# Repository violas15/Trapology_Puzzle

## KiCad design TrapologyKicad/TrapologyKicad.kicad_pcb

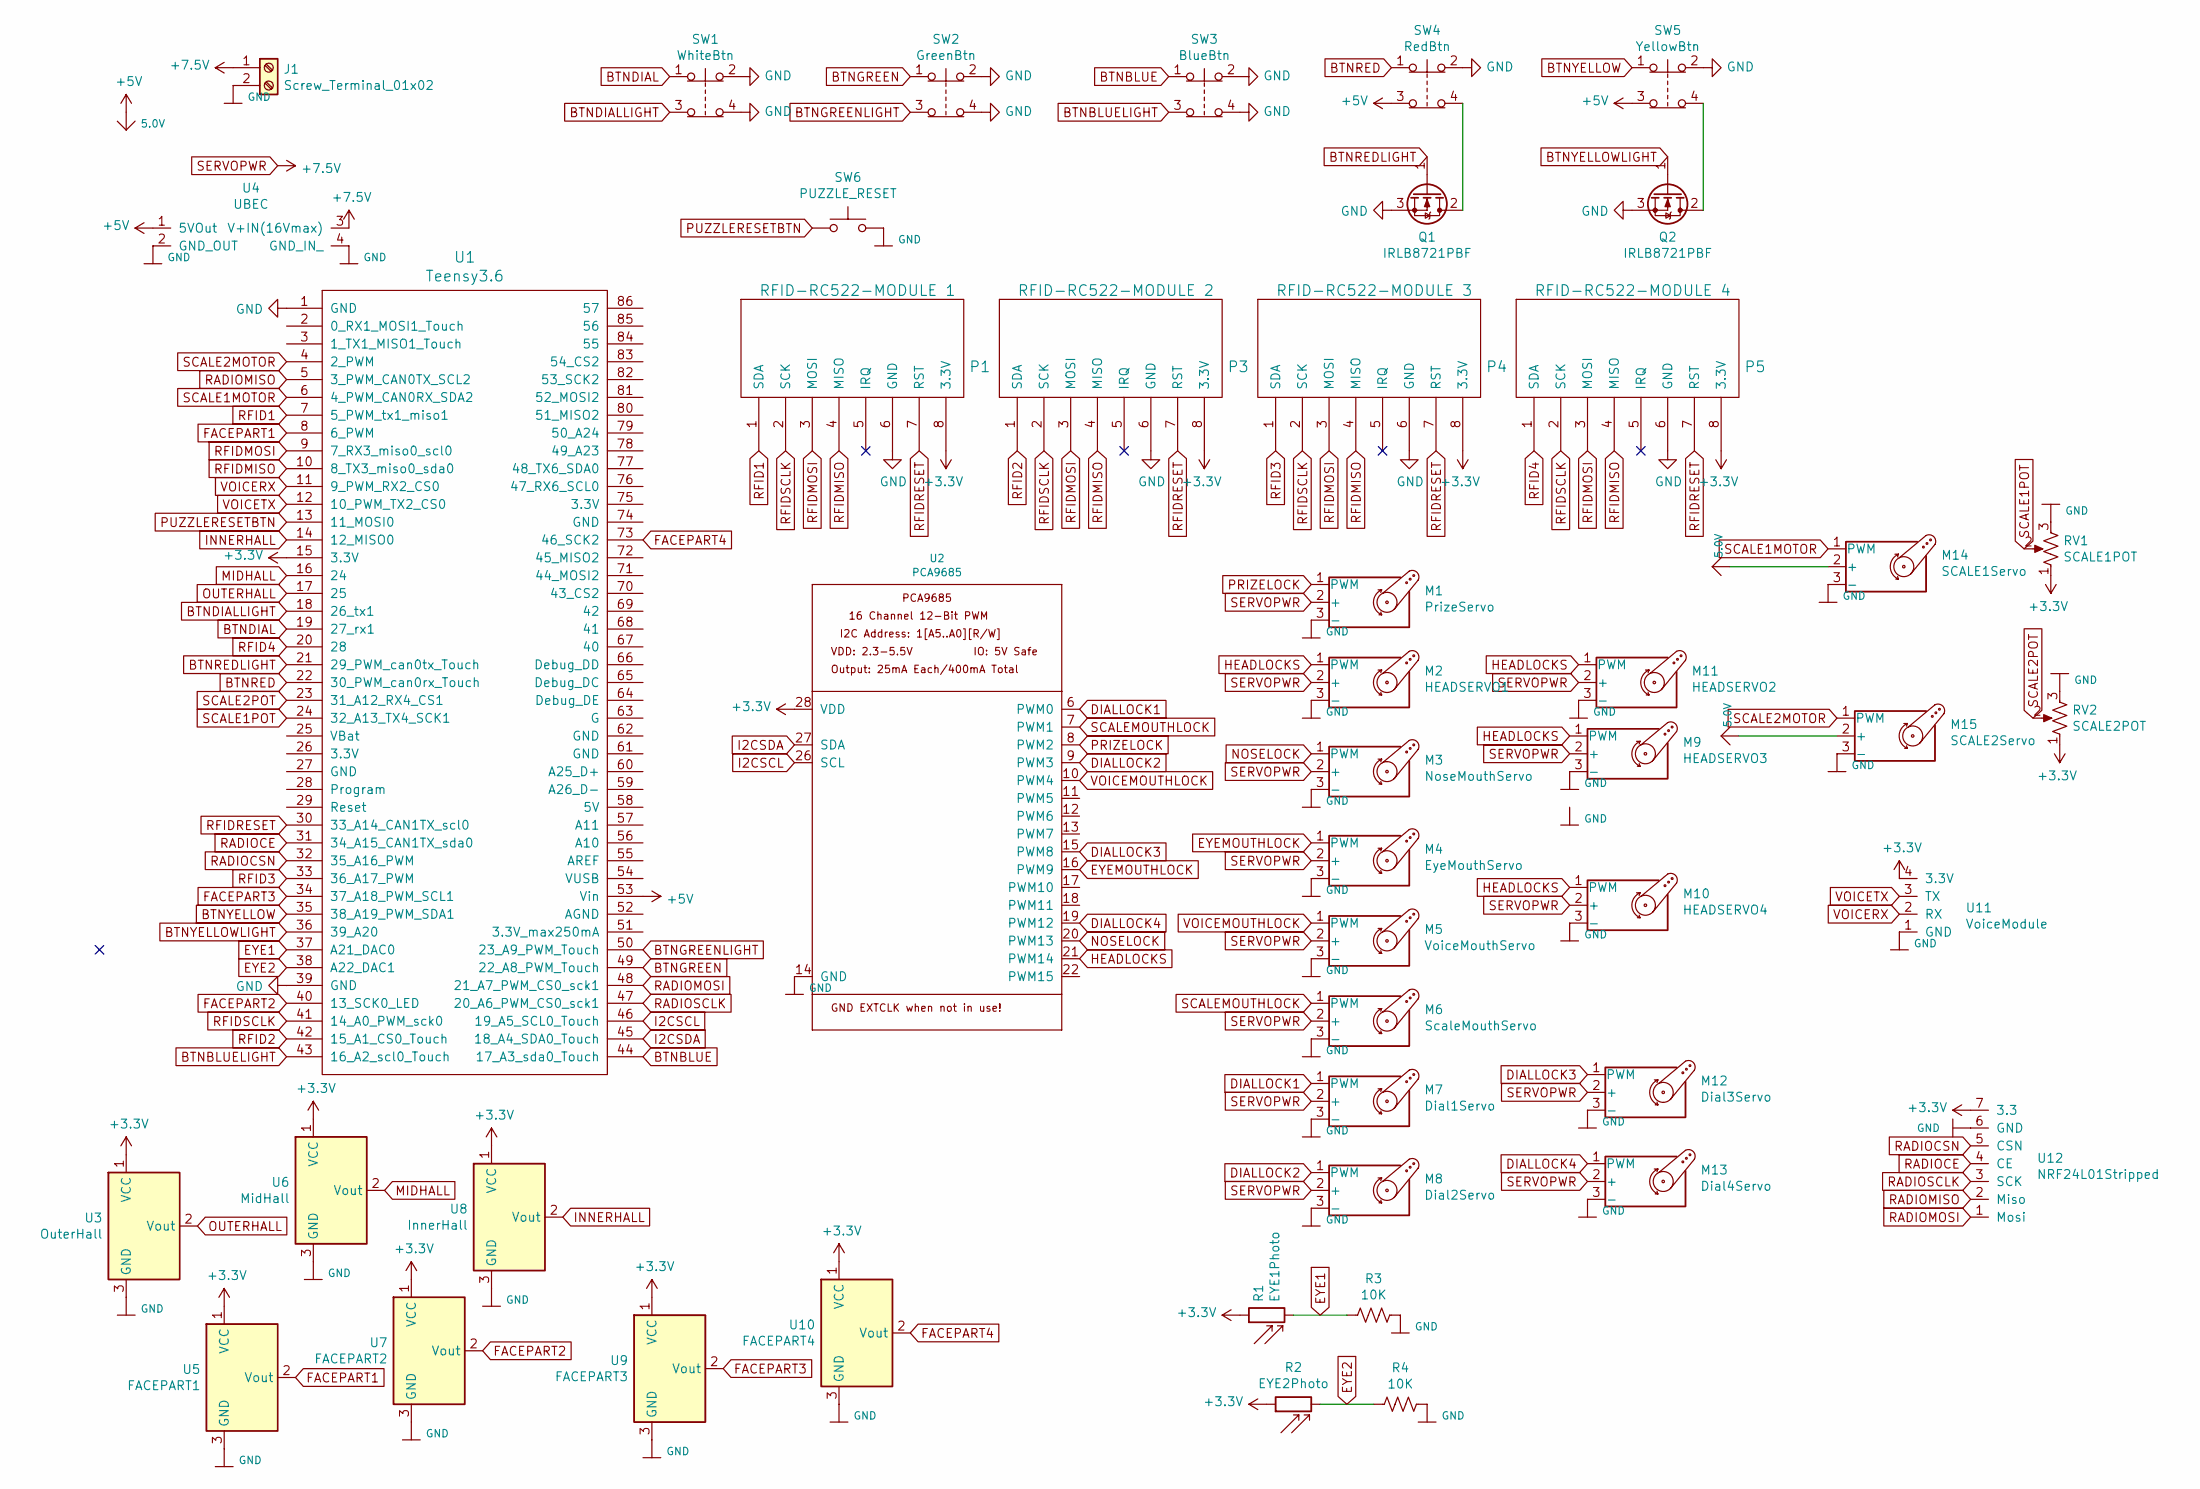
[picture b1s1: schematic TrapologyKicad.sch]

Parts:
J1: Screw_Terminal_01x02; TerminalBlock_Altech_AK300-2_P5.00mm
M1: PrizeServo; PinSocket_1x03_P2.54mm_Vertical
M2: HEADSERVO1; PinSocket_1x03_P2.54mm_Vertical
M3: NoseMouthServo; PinSocket_1x03_P2.54mm_Vertical
M4: EyeMouthServo; PinSocket_1x03_P2.54mm_Vertical
M5: VoiceMouthServo; PinSocket_1x03_P2.54mm_Vertical
M6: ScaleMouthServo; PinSocket_1x03_P2.54mm_Vertical
M7: Dial1Servo; PinSocket_1x03_P2.54mm_Vertical
M8: Dial2Servo; PinSocket_1x03_P2.54mm_Vertical
M9: HEADSERVO3; PinSocket_1x03_P2.54mm_Vertical
M10: HEADSERVO4; PinSocket_1x03_P2.54mm_Vertical
M11: HEADSERVO2; PinSocket_1x03_P2.54mm_Vertical
M12: Dial3Servo; PinSocket_1x03_P2.54mm_Vertical
M13: Dial4Servo; PinSocket_1x03_P2.54mm_Vertical
M14: SCALE1Servo; PinSocket_1x03_P2.54mm_Vertical
M15: SCALE2Servo; PinSocket_1x03_P2.54mm_Vertical
P1: RFID-RC522-MODULE 1; PinSocket_1x08_P2.54mm_Vertical
P3: RFID-RC522-MODULE 2; PinSocket_1x08_P2.54mm_Vertical
P4: RFID-RC522-MODULE 3; PinSocket_1x08_P2.54mm_Vertical
P5: RFID-RC522-MODULE 4; PinSocket_1x08_P2.54mm_Vertical
Q1, Q2: IRLB8721PBF; TO-220-3_Vertical
R1: EYE1Photo; PinSocket_1x02_P2.54mm_Vertical
R2: EYE2Photo; PinSocket_1x02_P2.54mm_Vertical
R3, R4: 10K; R_Axial_DIN0411_L9.9mm_D3.6mm_P12.70mm_Horizontal
RV1: SCALE1POT; PinSocket_1x03_P2.54mm_Vertical
RV2: SCALE2POT; PinSocket_1x03_P2.54mm_Vertical
SW1: WhiteBtn; PinSocket_1x04_P2.54mm_Vertical
SW2: GreenBtn; PinSocket_1x04_P2.54mm_Vertical
SW3: BlueBtn; PinSocket_1x04_P2.54mm_Vertical
SW4: RedBtn; PinSocket_1x04_P2.54mm_Vertical
SW5: YellowBtn; PinSocket_1x04_P2.54mm_Vertical
SW6: PUZZLE_RESET; PinSocket_1x02_P2.54mm_Vertical
U1: Teensy3.6; Teensy35_36
U2: PCA9685; 16ChannelPWM
U3: OuterHall; PinSocket_1x03_P2.54mm_Vertical
U4: UBEC
U5: FACEPART1; PinSocket_1x03_P2.54mm_Vertical
U6: MidHall; PinSocket_1x03_P2.54mm_Vertical
U7: FACEPART2; PinSocket_1x03_P2.54mm_Vertical
U8: InnerHall; PinSocket_1x03_P2.54mm_Vertical
U9: FACEPART3; PinSocket_1x03_P2.54mm_Vertical
U10: FACEPART4; PinSocket_1x03_P2.54mm_Vertical
U11: VoiceModule; PinSocket_1x04_P2.54mm_Vertical
U12: NRF24L01Stripped; PinSocket_1x07_P2.54mm_Vertical

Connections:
+3V3: P1.8 (3.3V), P3.8 (3.3V), P4.8 (3.3V), P5.8 (3.3V), R1.1, R2.1, RV1.1, RV2.1, U1.15 (3.3V), U2.28 (VDD), U3.1 (VCC), U5.1 (VCC), U6.1 (VCC), U7.1 (VCC), U8.1 (VCC), U9.1 (VCC), U10.1 (VCC), U11.4 (3.3V), U12.7 (3.3)
+5V: M14.2 (+), M15.2 (+), SW4.3, SW5.3, U1.53 (Vin), U4.1 (5VOut)
BTNBLUE: SW3.1, U1.44 (17_A3_sda0_Touch)
BTNBLUELIGHT: SW3.3, U1.43 (16_A2_scl0_Touch)
BTNDIAL: SW1.1, U1.19 (27_rx1)
BTNDIALLIGHT: SW1.3, U1.18 (26_tx1)
BTNGREEN: SW2.1, U1.49 (22_A8_PWM_Touch)
BTNGREENLIGHT: SW2.3, U1.50 (23_A9_PWM_Touch)
BTNRED: SW4.1, U1.22 (30_PWM_can0rx_Touch)
BTNREDLIGHT: Q1.1 (G), U1.21 (29_PWM_can0tx_Touch)
BTNYELLOW: SW5.1, U1.35 (38_A19_PWM_SDA1)
BTNYELLOWLIGHT: Q2.1 (G), U1.36 (39_A20)
DIALLOCK1: M7.1 (PWM), U2.6 (PWM0)
DIALLOCK2: M8.1 (PWM), U2.9 (PWM3)
DIALLOCK3: M12.1 (PWM), U2.15 (PWM8)
DIALLOCK4: M13.1 (PWM), U2.19 (PWM12)
EYE1: R1.2, R3.2, U1.37 (A21_DAC0)
EYE2: R2.2, R4.2, U1.38 (A22_DAC1)
EYEMOUTHLOCK: M4.1 (PWM), U2.16 (PWM9)
FACEPART1: U1.8 (6_PWM), U5.2 (Vout)
FACEPART2: U1.40 (13_SCK0_LED), U7.2 (Vout)
FACEPART3: U1.34 (37_A18_PWM_SCL1), U9.2 (Vout)
FACEPART4: U1.73 (46_SCK2), U10.2 (Vout)
GND: J1.2, M1.3 (-), M2.3 (-), M3.3 (-), M4.3 (-), M5.3 (-), M6.3 (-), M7.3 (-), M8.3 (-), M9.3 (-), M10.3 (-), M11.3 (-), M12.3 (-), M13.3 (-), M14.3 (-), M15.3 (-), P1.6 (GND), P3.6 (GND), P4.6 (GND), P5.6 (GND), Q1.3 (S), Q2.3 (S), R3.1, R4.1, RV1.3, RV2.3, SW1.2, SW1.4, SW2.2, SW2.4, SW3.2, SW3.4, SW4.2, SW5.2, SW6.2, U1.1 (GND), U1.39 (GND), U2.14 (GND), U3.3 (GND), U4.2 (GND_OUT), U4.4 (GND_IN_), U5.3 (GND), U6.3 (GND), U7.3 (GND), U8.3 (GND), U9.3 (GND), U10.3 (GND), U11.1 (GND), U12.6 (GND)
HEADLOCKS: M2.1 (PWM), M9.1 (PWM), M10.1 (PWM), M11.1 (PWM), U2.21 (PWM14)
I2CSCL: U1.46 (19_A5_SCL0_Touch), U2.26 (SCL)
I2CSDA: U1.45 (18_A4_SDA0_Touch), U2.27 (SDA)
INNERHALL: U1.14 (12_MISO0), U8.2 (Vout)
MIDHALL: U1.16 (24), U6.2 (Vout)
NOSELOCK: M3.1 (PWM), U2.20 (PWM13)
unnamed: Q1.2 (D), SW4.4
unnamed: Q2.2 (D), SW5.4
OUTERHALL: U1.17 (25), U3.2 (Vout)
PRIZELOCK: M1.1 (PWM), U2.8 (PWM2)
PUZZLERESETBTN: SW6.1, U1.13 (11_MOSI0)
RADIOCE: U1.31 (34_A15_CAN1TX_sda0), U12.4 (CE)
RADIOCSN: U1.32 (35_A16_PWM), U12.5 (CSN)
RADIOMISO: U1.5 (3_PWM_CAN0TX_SCL2), U12.2 (Miso)
RADIOMOSI: U1.48 (21_A7_PWM_CS0_sck1), U12.1 (Mosi)
RADIOSCLK: U1.47 (20_A6_PWM_CS0_sck1), U12.3 (SCK)
RFID1: P1.1 (SDA), U1.7 (5_PWM_tx1_miso1)
RFID2: P3.1 (SDA), U1.42 (15_A1_CS0_Touch)
RFID3: P4.1 (SDA), U1.33 (36_A17_PWM)
RFID4: P5.1 (SDA), U1.20 (28)
RFIDMISO: P1.4 (MISO), P3.4 (MISO), P4.4 (MISO), P5.4 (MISO), U1.10 (8_TX3_miso0_sda0)
RFIDMOSI: P1.3 (MOSI), P3.3 (MOSI), P4.3 (MOSI), P5.3 (MOSI), U1.9 (7_RX3_miso0_scl0)
RFIDRESET: P1.7 (RST), P3.7 (RST), P4.7 (RST), P5.7 (RST), U1.30 (33_A14_CAN1TX_scl0)
RFIDSCLK: P1.2 (SCK), P3.2 (SCK), P4.2 (SCK), P5.2 (SCK), U1.41 (14_A0_PWM_sck0)
SCALE1MOTOR: M14.1 (PWM), U1.6 (4_PWM_CAN0RX_SDA2)
SCALE1POT: RV1.2, U1.24 (32_A13_TX4_SCK1)
SCALE2MOTOR: M15.1 (PWM), U1.4 (2_PWM)
SCALE2POT: RV2.2, U1.23 (31_A12_RX4_CS1)
SCALEMOUTHLOCK: M6.1 (PWM), U2.7 (PWM1)
SERVOPWR: J1.1, M1.2 (+), M2.2 (+), M3.2 (+), M4.2 (+), M5.2 (+), M6.2 (+), M7.2 (+), M8.2 (+), M9.2 (+), M10.2 (+), M11.2 (+), M12.2 (+), M13.2 (+), U4.3 (V+IN(16Vmax))
VOICEMOUTHLOCK: M5.1 (PWM), U2.10 (PWM4)
VOICERX: U1.11 (9_PWM_RX2_CS0), U11.2 (RX)
VOICETX: U1.12 (10_PWM_TX2_CS0), U11.3 (TX)

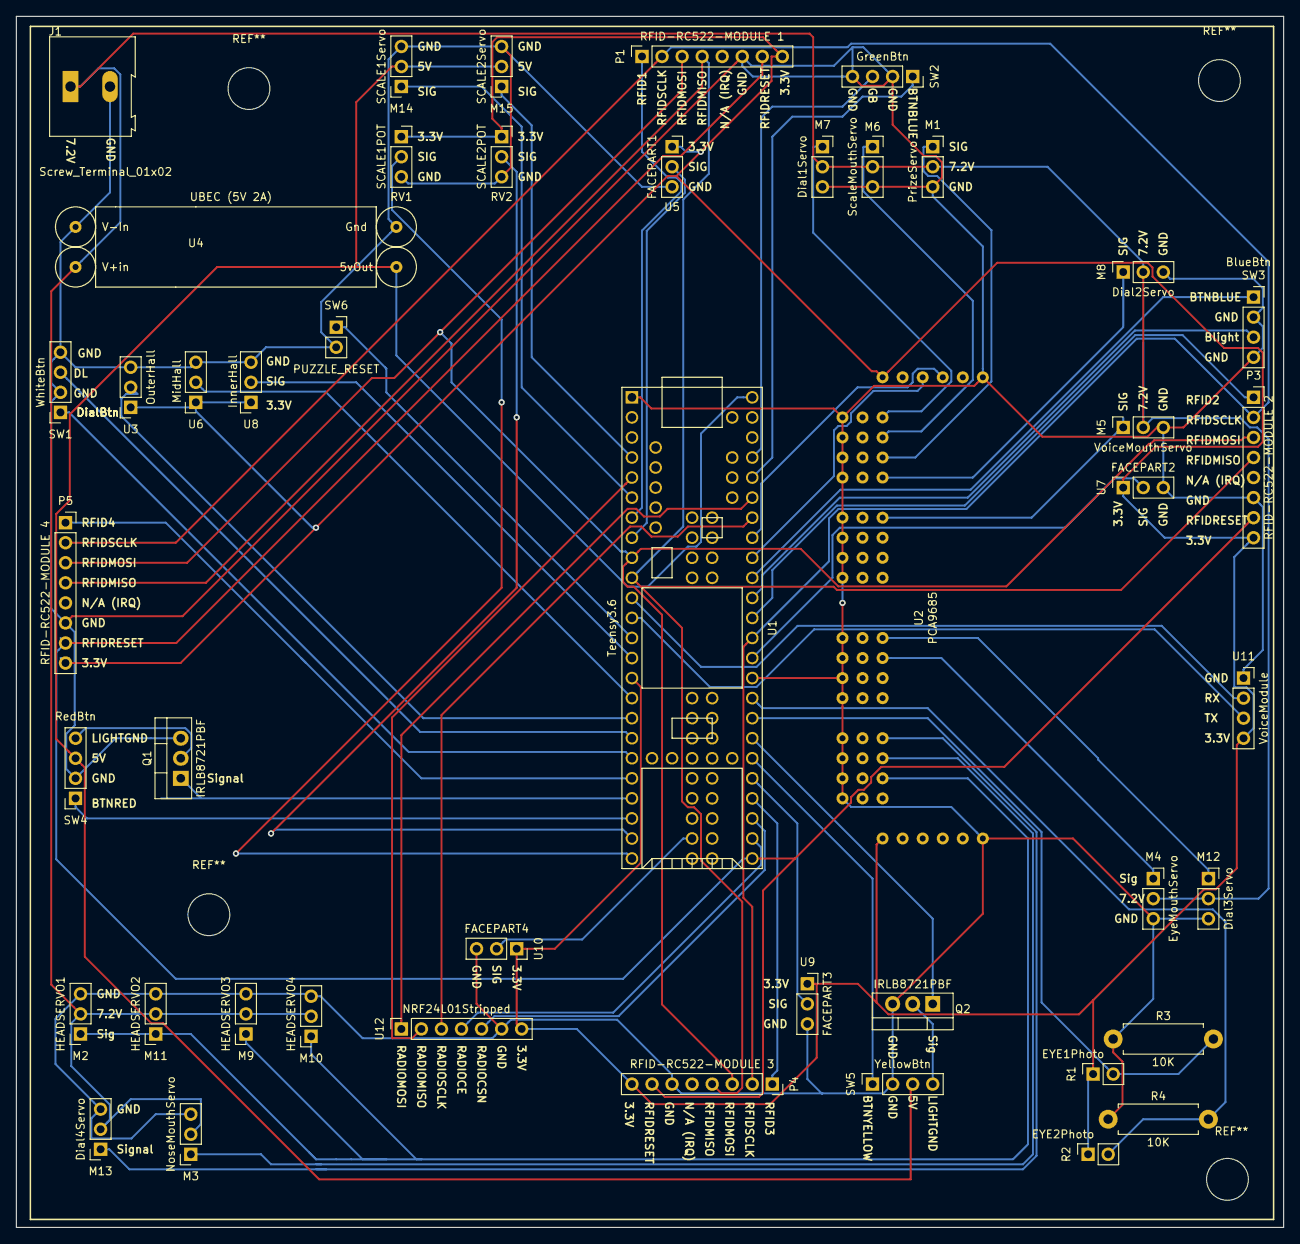
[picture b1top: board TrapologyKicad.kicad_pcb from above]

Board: 2 copper layers, 160.5 x 153.4 mm, 46 parts (0 on the bottom side), 57 nets.

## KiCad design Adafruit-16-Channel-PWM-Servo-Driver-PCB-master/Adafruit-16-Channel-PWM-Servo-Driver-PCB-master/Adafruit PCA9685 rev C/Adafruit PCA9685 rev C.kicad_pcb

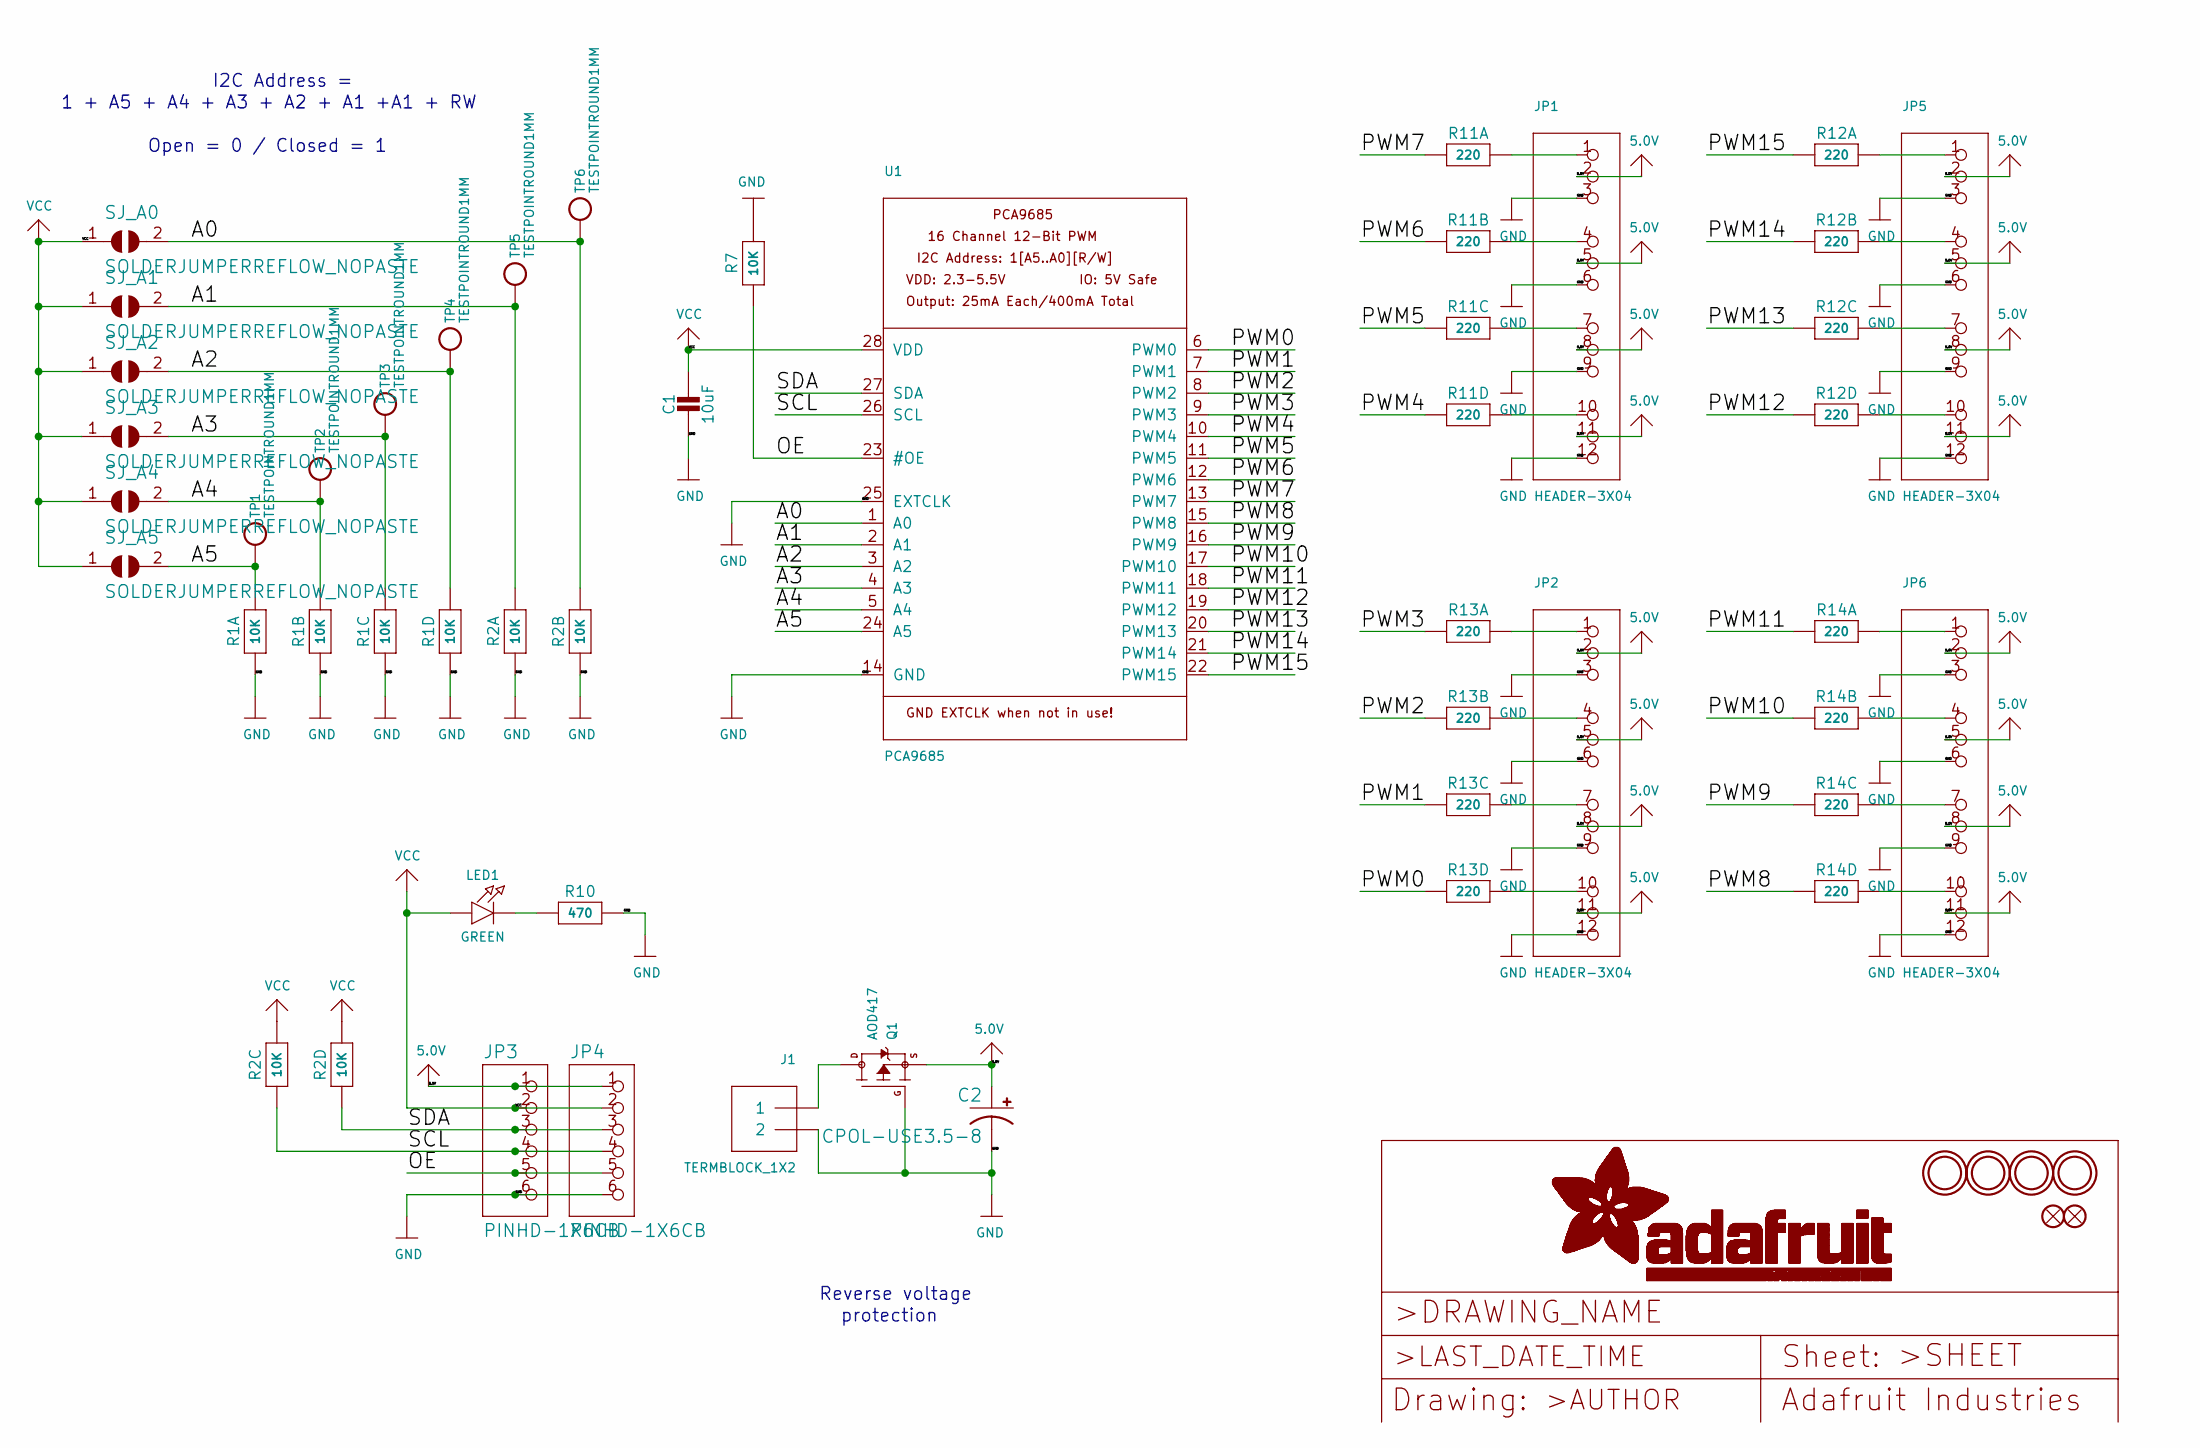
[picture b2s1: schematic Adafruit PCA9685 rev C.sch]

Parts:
C1: 10uF; 0805-NO
C2: CPOL-USE3.5-8; E3,5-8
FID1, FID2: FIDUCIAL\"\"; FIDUCIAL_1MM
J1: TERMBLOCK_1X2; TERMBLOCK_1X2-3.5MM
JP1, JP2, JP5, JP6: HEADER-3X04; 3X04
JP3, JP4: PINHD-1X6CB; 1X06-CLEANBIG
LED1: GREEN; CHIPLED_0805_NOOUTLINE
Q1: AOD417; TO252
R1, R2: 10K; RESPACK_4X0603
R7: 10K; 0805-NO
R10: 470; _0805MP
R11, R12, R13, R14: 220; RESPACK_4X0603
SJ_A0, SJ_A1, SJ_A2, SJ_A3, SJ_A4, SJ_A5: SOLDERJUMPERREFLOW_NOPASTE; SOLDERJUMPER_REFLOW_NOPASTE
TP1, TP2, TP3, TP4, TP5, TP6: TESTPOINTROUND1MM; TESTPOINT_ROUND_1MM
U1: PCA9685; TSSOP28
U$47, U$48, U$49, U$50: MOUNTINGHOLE2.5; MOUNTINGHOLE_2.5_PLATED

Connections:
5.0V: C2.+, JP1.2, JP1.5, JP1.8, JP1.11, JP2.2, JP2.5, JP2.8, JP2.11, JP3.1, JP4.1, JP5.2, JP5.5, JP5.8, JP5.11, JP6.2, JP6.5, JP6.8, JP6.11, Q1.2 (S)
/A0: R2.7 (2), SJ_A0.2, TP6.P$1, U1.1 (A0)
/A1: R2.8 (2), SJ_A1.2, TP5.P$1, U1.2 (A1)
/A2: R1.5 (2), SJ_A2.2, TP4.P$1, U1.3 (A2)
/A3: R1.6 (2), SJ_A3.2, TP3.P$1, U1.4 (A3)
/A4: R1.7 (2), SJ_A4.2, TP2.P$1, U1.5 (A4)
/A5: R1.8 (2), SJ_A5.2, TP1.P$1, U1.24 (A5)
/OE: JP3.5, JP4.5, R7.1, U1.23 (#OE)
/PWM0: R13.4 (1), U1.6 (PWM0)
/PWM1: R13.3 (1), U1.7 (PWM1)
/PWM2: R13.2 (1), U1.8 (PWM2)
/PWM3: R13.1, U1.9 (PWM3)
/PWM4: R11.4 (1), U1.10 (PWM4)
/PWM5: R11.3 (1), U1.11 (PWM5)
/PWM6: R11.2 (1), U1.12 (PWM6)
/PWM7: R11.1, U1.13 (PWM7)
/PWM8: R14.4 (1), U1.15 (PWM8)
/PWM9: R14.3 (1), U1.16 (PWM9)
/PWM10: R14.2 (1), U1.17 (PWM10)
/PWM11: R14.1, U1.18 (PWM11)
/PWM12: R12.4 (1), U1.19 (PWM12)
/PWM13: R12.3 (1), U1.20 (PWM13)
/PWM14: R12.2 (1), U1.21 (PWM14)
/PWM15: R12.1, U1.22 (PWM15)
/SCL: JP3.4, JP4.4, R2.3 (1), U1.26 (SCL)
/SDA: JP3.3, JP4.3, R2.4 (1), U1.27 (SDA)
GND: C1.2, C2.-, J1.2, JP1.3, JP1.6, JP1.9, JP1.12, JP2.3, JP2.6, JP2.9, JP2.12, JP3.6, JP4.6, JP5.3, JP5.6, JP5.9, JP5.12, JP6.3, JP6.6, JP6.9, JP6.12, Q1.1 (G), R1.1, R1.2 (1), R1.3 (1), R1.4 (1), R2.1, R2.2 (1), R7.2, R10.2, U1.14 (GND), U1.25 (EXTCLK)
unnamed: J1.1, Q1.3 (D)
unnamed: JP1.1, R11.8 (2)
unnamed: JP1.4, R11.7 (2)
unnamed: JP1.7, R11.6 (2)
unnamed: JP1.10, R11.5 (2)
unnamed: JP2.1, R13.8 (2)
unnamed: JP2.4, R13.7 (2)
unnamed: JP2.7, R13.6 (2)
unnamed: JP2.10, R13.5 (2)
unnamed: JP5.1, R12.8 (2)
unnamed: JP5.4, R12.7 (2)
unnamed: JP5.7, R12.6 (2)
unnamed: JP5.10, R12.5 (2)
unnamed: JP6.1, R14.8 (2)
unnamed: JP6.4, R14.7 (2)
unnamed: JP6.7, R14.6 (2)
unnamed: JP6.10, R14.5 (2)
unnamed: LED1.C, R10.1
VCC: C1.1, JP3.2, JP4.2, LED1.A, R2.5 (2), R2.6 (2), SJ_A0.1, SJ_A1.1, SJ_A2.1, SJ_A3.1, SJ_A4.1, SJ_A5.1, U1.28 (VDD)

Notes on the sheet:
Reverse voltage
protection
1 + A5 + A4 + A3 + A2 + A1 +A1 + RW
I2C Address =
Open = 0 / Closed = 1

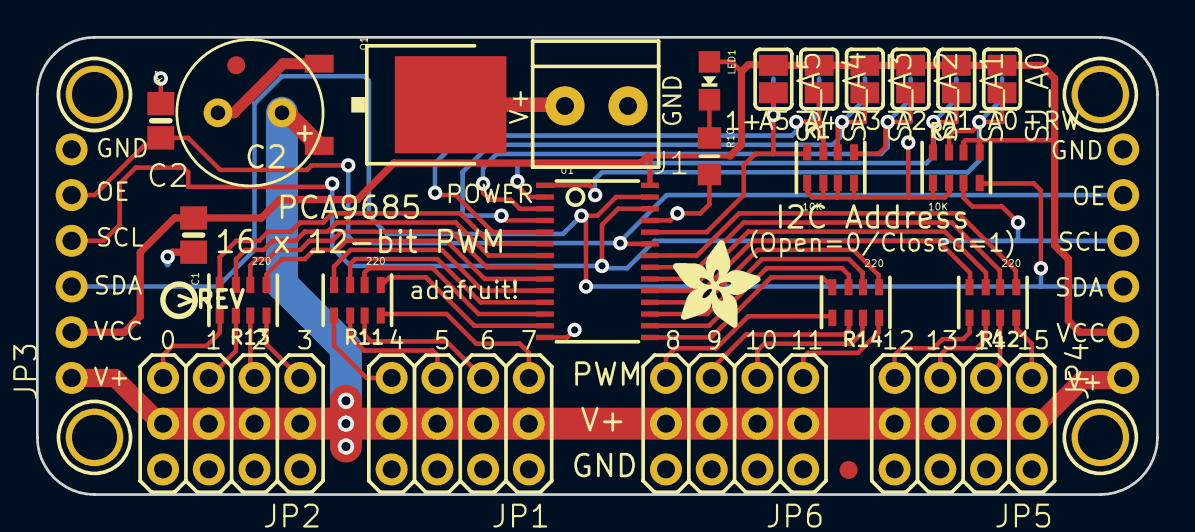
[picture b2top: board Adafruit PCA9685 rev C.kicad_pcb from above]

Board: 2 copper layers, 62.2 x 25.4 mm, 40 parts (0 on the bottom side), 46 nets.

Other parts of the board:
U$51: ADAFRUIT_5MM
U$54: PCBFEAT-REV-040

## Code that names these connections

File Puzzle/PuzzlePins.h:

#ifndef PUZZLE_PINS_H
#define PUZZLE_PINS_H
//SIDE 1 is the side with the scale hands green
//SIDE 2 is for the voice recognition module in ear blue
//SIDE 3 is photoresistors in the eyes yellow
//SIDE 4 is the swapping body part side red btn



//RFID Setup********************************************************************

#define RFIDSCLK 14
#define RFIDMISO 8
#define RFIDMOSI 7
#define RFIDRESET 38

#define RFID1 33
#define RFID1IDX 1
#define RFID1ANSWER "FDCDD183"

#define RFID2 34
#define RFID2IDX 2
#define RFID2ANSWER "36B77AF7"

#define RFID3 35
#define RFID3IDX 3
#define RFID3ANSWER "6917C820"

#define RFID4 36
#define RFID4IDX 4
#define RFID4ANSWER "9934BE20"

#define RFIDNOSE 37
#define RFIDNOSEIDX 0
#define RFIDNOSEANSWER "66987CF7"
//make sure to update puzzle.ino correctids if add more rfids
#define NUMREADERS 5 ///Change this to reflect number of RFID sensors connected
//END RFID SETUP****************************************************************

//solenoid setup****************************************************************
#define SCALEMOUTHLOCK 32 
#define VOICEMOUTHLOCK 31
#define EYEMOUTHLOCK 30
#define NOSELOCK 29
#define HEADLOCKS 28 //this is actually 4 solenoids actuated by realy
#define DIALDRAWERLOCK 27
#define PRIZELOCK 26
//end solenoid setup************************************************************

//Dial Hall effect setup *******************************************************
//https://www.adafruit.com/product/158?gclid=CjwKCAiAjNjgBRAgEiwAGLlf2qn13g8NA4FpkffIYcW2ZVwQ-Q3Ns69BRBwBOoz19MAtaabW1XeOIhoCp6gQAvD_BwE
#define OUTERHALL A21 //needs 10k resistor to power on 3rd leg
#define MIDHALL A22 
#define INNERHALL A20 //also digital pin 39
//******************************************************************************

//Photoresistors ***************************************************************
#define EYE1 19 //needs 10k resistor to ground
// #define EYE2 18 //needs 10k resistor to ground
//******************************************************************************

//Voice Module *****************************************************************
#define VOICETX 10 //tx on teensy
#define VOICERX 9 //rx on teensy
#define VOICESERIAL Serial2
#define VOICECORRECTIDX 7
//http://www.veear.eu/files/archive/EasyVR%203%20User%20Manual%201.0.9.pdf
//******************************************************************************

//Scale*************************************************************************
#define SCALE1MOTOR 23 //pwm
#define SCALE2MOTOR 22 //pwm
#define SCALE1POT 21
#define SCALE2POT 20
#define SCALE1VALUE 1000
#define SCALE2VALUE 500
//*********************************************************************************

//Button Setup*********************************************************************
#define BTNDIAL 24 //white //should be wired one end to gnd and the other to the correct pin
#define BTNDIALLIGHT 25

#define BTNRED 17
#define BTNREDLIGHT 16

#define BTNBLUE 15
#define BTNBLUELIGHT 13

#define BTNGREEN 2
#define BTNGREENLIGHT 3

#define BTNYELLOW 4
#define BTNYELLOWLIGHT 5
#define NUMBTNS 4

//**********************************************************************************

#define FOGRELAY 11
#define LEDRELAY 12


//SIMON
#define MAX_LEVEL 5


#endif

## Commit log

2019-01-24 added pcb files
